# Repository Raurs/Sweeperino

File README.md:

# Sweeperino
Eagle files for Sweeperino

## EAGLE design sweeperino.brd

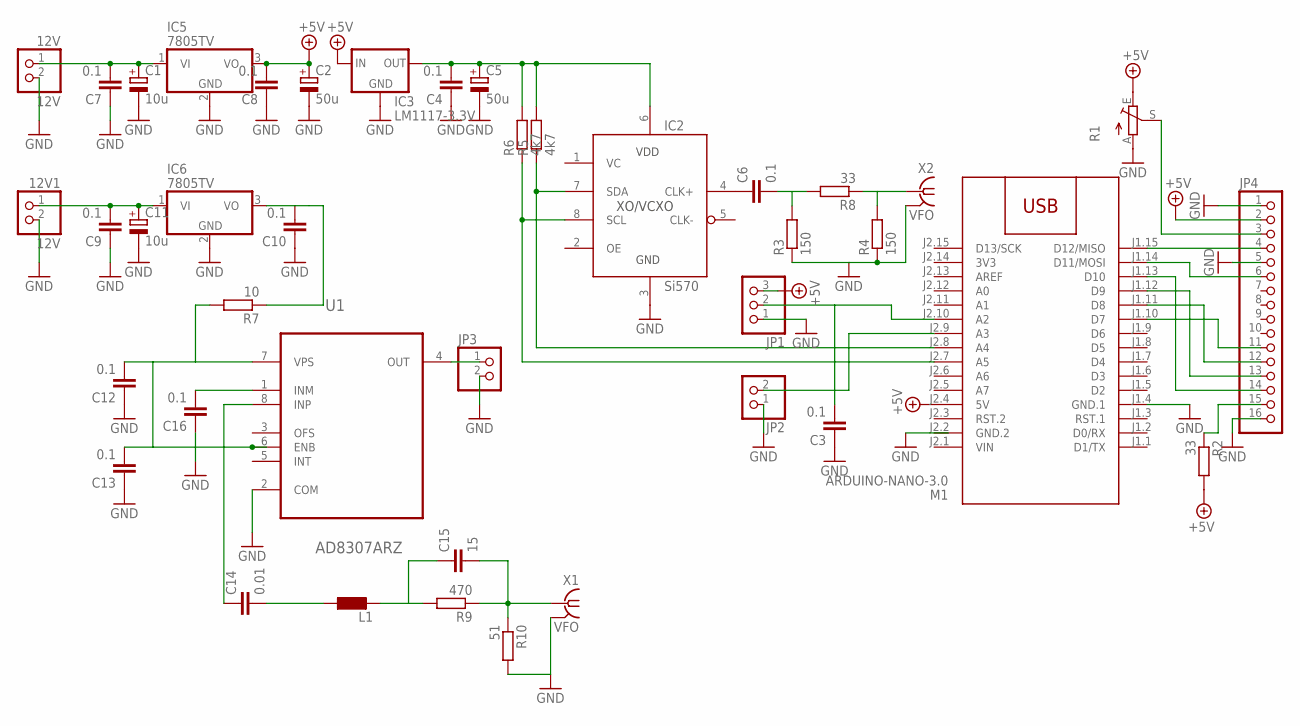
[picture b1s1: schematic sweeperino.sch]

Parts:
12V, 12V1: 12V; 1X02
C1, C11: 10u; E2,5-5
C2, C5: 50u; E2,5-5
C3, C4, C6, C7, C8, C9, C10, C12, C13, C16: 0.1; C050-024X044
C14: 0.01; C050-024X044
C15: 15; C050-024X044
IC2: Si570; SI57X
IC3: LM1117-3.3V; TO252
IC5, IC6: 7805TV; TO220V
JP1: PINHD-1X3; 1X03
JP2, JP3: PINHD-1X2; 1X02
JP4: PINHD-1X16; 1X16
L1: L0204/7; 0204/7
M1: ARDUINO-NANO-3.0
R1: TRIM_EU-CA6V; CA6V
R2, R8: 33; 0204/5
R3, R4: 150; 0204/5
R5, R6: 4k7; 0204/5
R7: 10; 0204/5
R9: 470; 0204/5
R10: 51; 0204/5
U1: AD8307ARZ; SOIC127P600X175-8N
X1, X2: VFO; BU-SMA-V

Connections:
3V3: M1.J2.14 (3V3)
+5V: C2.+, C8.2, IC3.2 (IN), IC5.3 (VO), JP1.3, JP4.2, M1.J2.4 (5V), R1.E, R2.2
GND: 12V.2, 12V1.2, C1.-, C2.-, C3.1, C4.1, C5.-, C7.1, C8.1, C9.1, C10.1, C11.-, C12.1, C13.1, C16.1, IC2.3 (GND), IC3.1 (GND), IC5.2 (GND), JP1.1, JP2.1, JP3.2, JP4.1, JP4.5, JP4.16, M1.J1.4 (GND.1), R1.A, R3.1, R4.1, R10.2, U1.2 (COM), X1.2 (GND), X1.3 (GND), X1.4 (GND), X1.5 (GND), X2.2 (GND), X2.3 (GND), X2.4 (GND), X2.5 (GND)
GND.2: M1.J2.2 (GND.2)
unnamed: JP3.1, U1.4 (OUT)
unnamed: C10.2, IC6.3 (VO), R7.1
unnamed: C14.1, U1.8 (INP)
unnamed: C3.2, JP1.2, M1.J2.10 (A2)
unnamed: JP4.3, R1.S
unnamed: JP4.4, M1.J1.15 (D12/MISO)
unnamed: JP4.6, M1.J1.14 (D11/MOSI)
unnamed: JP4.11, M1.J1.10 (D7)
unnamed: JP4.12, M1.J1.11 (D8)
unnamed: JP4.13, M1.J1.12 (D9)
unnamed: C6.2, R3.2, R8.2
unnamed: R4.2, R8.1, X2.1
unnamed: JP4.14, M1.J1.13 (D10)
unnamed: JP4.15, R2.1
unnamed: 12V1.1, C9.2, C11.+, IC6.1 (VI)
unnamed: C12.2, C13.2, R7.2, U1.6 (ENB), U1.7 (VPS)
unnamed: JP2.2, M1.J2.9 (A3)
unnamed: C14.2, L1.1
unnamed: IC2.7 (SDA), M1.J2.8 (A4), R5.1
unnamed: IC2.8 (SCL), M1.J2.7 (A5), R6.1
unnamed: C4.2, C5.+, IC2.6 (VDD), IC3.3 (OUT), R5.2, R6.2
unnamed: C6.1, IC2.4 (CLK+)
unnamed: C15.1, L1.2, R9.2
unnamed: C16.2, U1.1 (INM)
unnamed: C15.2, R9.1, R10.1, X1.1
unnamed: 12V.1, C1.+, C7.2, IC5.1 (VI)
VIN: M1.J2.1 (VIN)

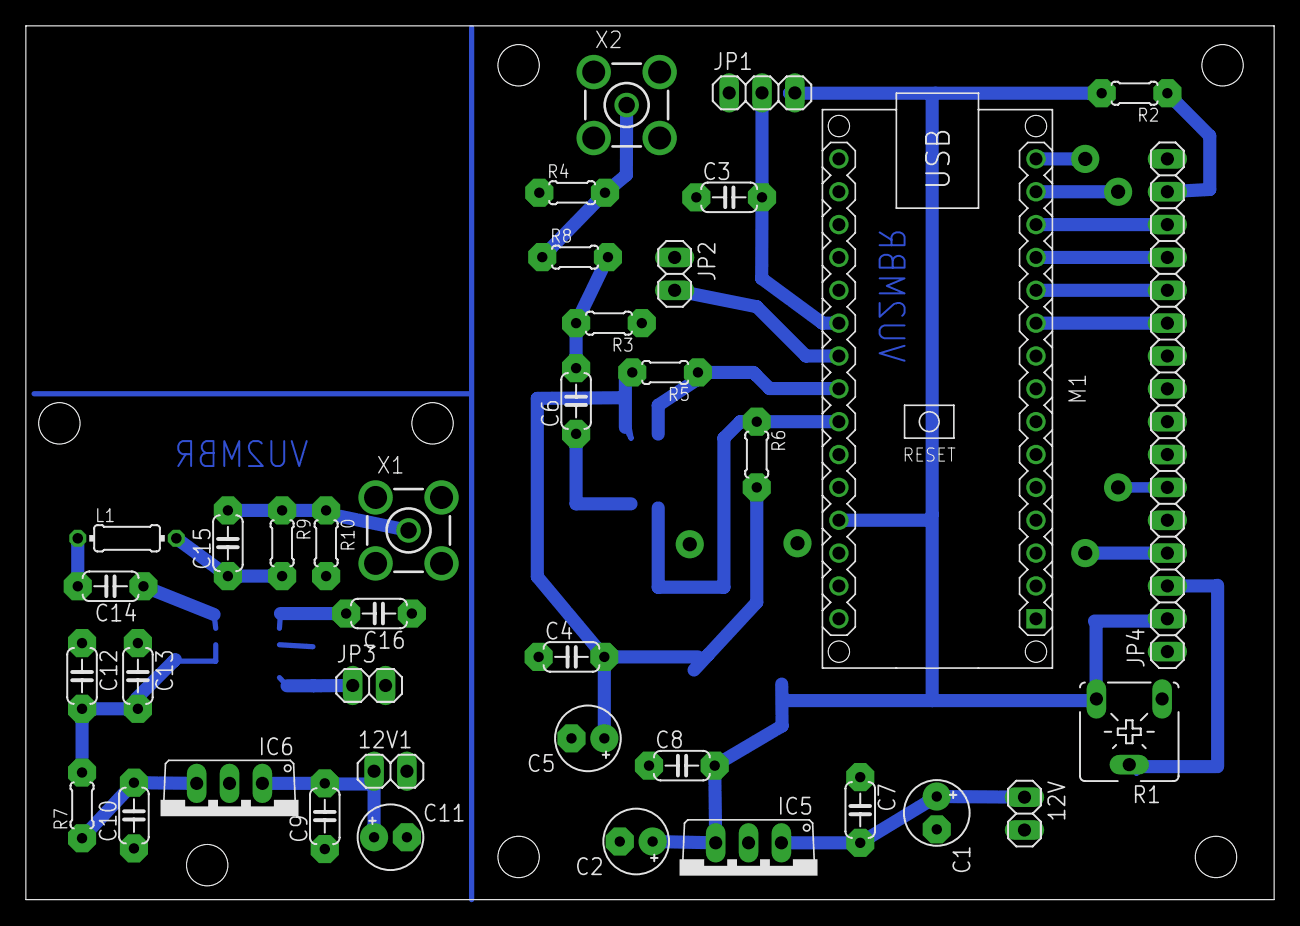
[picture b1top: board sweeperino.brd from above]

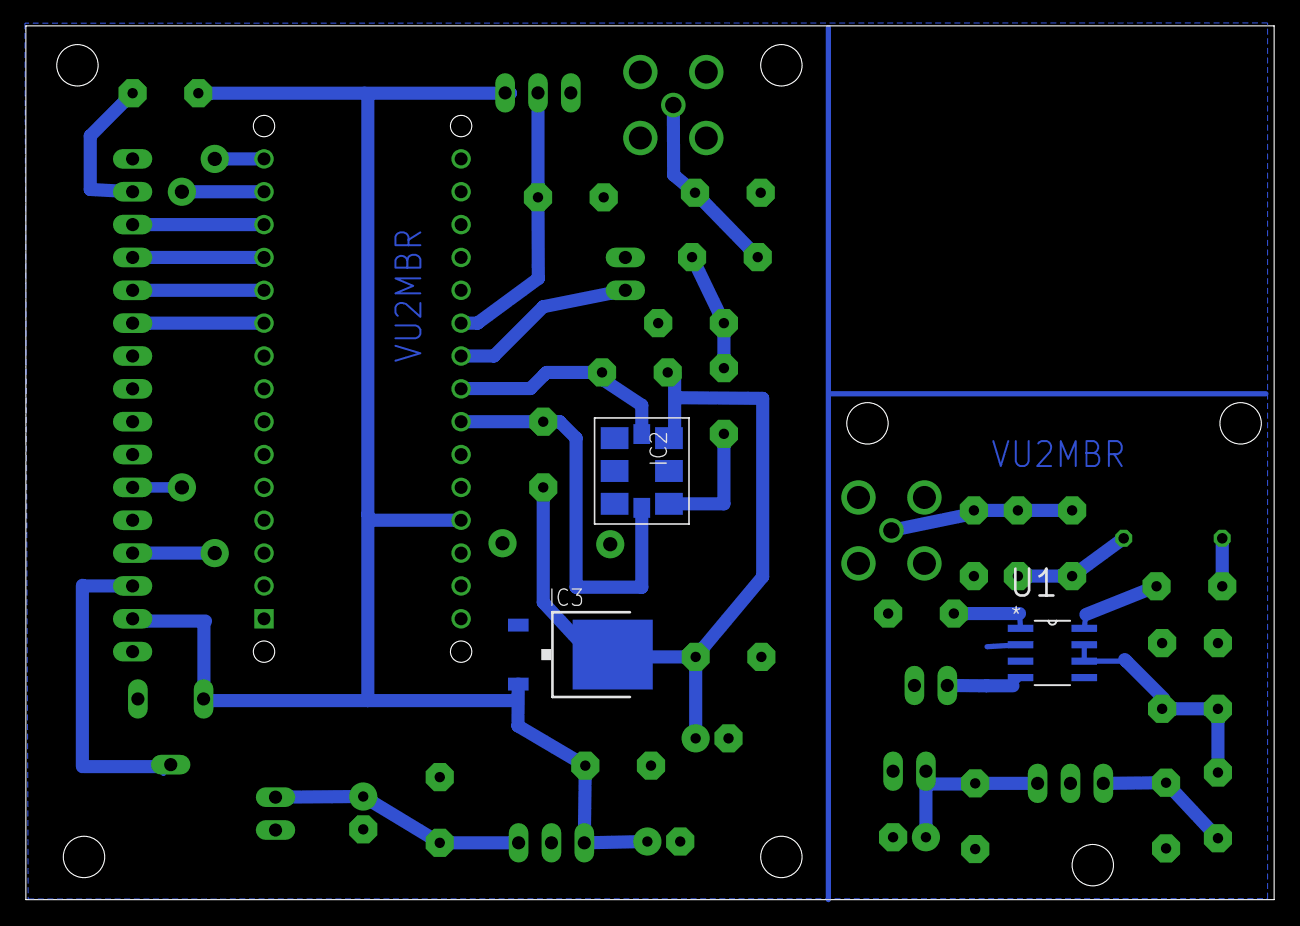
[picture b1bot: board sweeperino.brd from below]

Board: 2 copper layers, 96.5 x 67.6 mm, 41 parts (3 on the bottom side), 28 nets.

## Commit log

2015-12-29 Commit-1
2016-01-03 Updated board

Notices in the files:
parts and their libraries:
diy-modules: Released under the Creative Commons Attribution 4.0 International License: http://creativecommons.org/licenses/by/4.0
